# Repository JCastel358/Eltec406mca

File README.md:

# Eltec sensor test rigs

Bench rigs and software that qualify Eltec pyroelectric IR sensors. Two rigs
live in this repository, one top-level folder each:

- **`single_detector_rig/`** — an ESP32 chops an IR emitter and streams a
  24-bit ADS1256 ADC to a laptop; one Python desktop application runs the
  test procedure for the sensor model chosen in a dropdown, judges each part,
  and writes a CSV row per sensor.
- **`array_rig/`** — fifty detectors at once: a 50-position buffer PCB read
  by an ACCES USB-AIO16-64MA DAQ; the same selector-plus-model-directory
  structure, testing offset and noise per tray (sensitivity waits for the
  emitter board).

Windows 11 and Xubuntu are both supported.

The current **M25/HUB array** workflow is available from the normal Array Rig
launcher: selectable offset/noise tests, simultaneous recording at 80% settled
(90-second fallback), linked retests, persistent slot warnings, and saved
50-position reports. See [the current array instructions](array_rig/README.md).
Real M25/HUB acquisition uses Windows and the ACCES driver; simulation also
runs without hardware. No Arduino/ESP32 flash is needed for this offset/noise
check. Earlier contiguous-channel instructions are the explicit legacy profile.

| Sensor model | Procedure | Status (2026-09-02) | Results folder (`Documents\…`) |
| --- | --- | --- | --- |
| **405 M22** (1 Hz) | TP412 — offset, emitter-off noise, sensitivity/polarity | production; sensitivity factor 4.30 from lot 500 | `Eltec_405M22_Test_Results\405m22_esp32` |
| **406 MCA** (10 Hz) | offset, sensitivity/polarity, v6.1 stability policy | production; factor 1.582 from lot 520 | `Eltec_406MCA_Test_Results\v6_1_esp32` |
| **449 M18** (5 + 18 Hz) | TP443 frequency tracking | **calibration pending** (K_5 / K_18 not derived; needs firmware v3.2, not yet flashed) | `Eltec_449M18_Test_Results\449m18_esp32` |
| **40623 array** (50 positions, DAQ) | TP120 offset check + noise, fifty at a time | **calibration pending** (noise limits not derived, offset limits provisional; raw captures saved for the paired lot) | `Eltec_40623_Test_Results\40623_array_daq` |

---

## Set up another Windows computer

1. Install **64-bit Python with Tcl/Tk and pip**, and enable its PATH option.
   The software check for this update used Python **3.14.5**. Install Git if
   you want to clone/pull updates; GitHub's Download ZIP also works.
2. Clone the repository, or run `git pull --ff-only` in an existing clean
   checkout. In PowerShell, from the repository root:

   ```powershell
   git clone -c core.longpaths=true https://github.com/JCastel358/Eltec406mca.git
   cd Eltec406mca
   python -m pip install -r requirements.txt
   python -c "import struct, tkinter, numpy, serial, matplotlib; print('Python bits:', struct.calcsize('P') * 8)"
   ```

   The clone option enables Git's Windows long-path support for the archived
   hardware exports. Keep the checkout path short; for an existing checkout,
   run `git config core.longpaths true` before pulling if Git reports
   "Filename too long". The bitness check must print **64** for real DAQ operation. Install into
   the same Python used to launch the app. If multiple Pythons are installed,
   set `ELTEC_PYTHON` to that interpreter's full executable path before using
   a `.cmd` launcher (the launchers otherwise prefer `pythonw.exe` on PATH).
3. For the **M25/HUB array**, install the ACCES **USB-AIO16-64MA driver
   package**, including the 64-bit `AIOUSB.dll`. Drivers are installed per PC
   and are not included in Git. This workflow runs on Windows and does not
   require Arduino, an ESP32 flash, or the separate `50AmpBoard` checkout.
   For the **single-detector rig**, install the board's USB-serial driver if
   needed and select its actual COM port; it may differ on the new computer.
4. Check the array dashboard without hardware first:

   ```powershell
   python array_rig/eltec_array_tester.py --simulate
   ```

   Choose **Generated demo** and complete a batch. To run normally, use
   `array_rig/run_eltec_array_tester.cmd`; the single-detector launcher is
   `single_detector_rig/run_eltec_rig_tester.cmd`. Optional desktop shortcuts
   are created by each rig's `install_windows_launcher.ps1` on the new PC.
   Before real acquisition, follow the current [array power/setup procedure](array_rig/README.md).
5. **Transfer saved data separately if needed.** Git does not contain the
   `Documents/Eltec_*_Test_Results/` folders, including results, raw captures,
   and reference calibration files. Preserve their directory structure and
   originals; see the [data and backup guide](array_rig/docs/DATA_MAP.md).
   A new physical setup still needs its applicable reference checks; copying
   files does not establish calibration for changed hardware.

The MOD50 browser dashboard and its assets are included in the repository
and run locally. Node.js and Playwright are only for optional browser
regression tests, not for operating the app. Python packages and device
drivers must be installed before offline use. Source files, firmware snapshots,
hardware packages and documentation are included; local `tmp/` runs, caches
and generated measurement data are not new Git content.

## I'm a technician — run a batch

1. Laptop on AC power, ESP32 USB cable in, both batteries connected, no fans near the fixture.
2. Double-click the **Eltec Test Rig** desktop icon (or `single_detector_rig\run_eltec_rig_tester.cmd` / `.sh`). For a tray of fifty on the array rig use the **Eltec Array Rig** icon (`array_rig\run_eltec_array_tester.cmd` / `.sh`) — runbook §3b.
3. Pick the sensor model → **Start tester** → batch number, your name, filter setup → load a part → **Enter**.
4. Read the banner (PASS / PASS · NEAR LIMIT / FAIL) → load the next sensor →
   **Next (Enter)**. The number only advances when a part passes.

Everything else — verdicts, the Stop / Next buttons, where files go,
what to do when something fails — is in
**[array_rig/docs/TECHNICIAN_RUNBOOK.md](array_rig/docs/TECHNICIAN_RUNBOOK.md)**.

## I'm the engineer taking over

Start with **[array_rig/docs/ENGINEER_HANDOVER.md](array_rig/docs/ENGINEER_HANDOVER.md)** (what
you are inheriting, architecture, the copy-per-model rule, firmware lifecycle,
open work). Then **[array_rig/docs/CALIBRATION_RECORD.md](array_rig/docs/CALIBRATION_RECORD.md)**
before touching any limit.

## Repository map

```
README.md                    this file — the index
CHANGELOG.md                 dated history, newest first (one entry per behavioural change)
CLAUDE.md                    ground rules for AI-assisted sessions
run_all_tests.py|.cmd|.sh    runs every test suite of both rigs, prints a summary
array_rig/docs/
  TECHNICIAN_RUNBOOK.md      operator instructions
  ENGINEER_HANDOVER.md       engineering manual + open work
  CALIBRATION_RECORD.md      every limit/factor/gate state with provenance  ← source of truth for numbers
  DATA_MAP.md                where results & evidence live (outside the repo) + backup routine
  TP120(40623).pdf           test procedure of the 40623 (array rig); daq_usb_aio16_64ma/ = DAQ vendor docs
single_detector_rig/         THE single-detector application — selector + one directory per sensor model
  eltec_rig_tester.py        selector GUI (dropdown → launches the model app)
  sensor_versions.py         model registry + required firmware
  attempt_history.py         per-batch attempt log (shared)
  v1_single_sensor/          vendored signal-math engine (shared, frozen)
  m405m22/ m406mca/ m449m18/ one qualified tester each: GUI, backend, analysis, tests, launchers, README
  run_eltec_rig_tester.*     launchers; install_*_launcher.* = optional desktop icon
array_rig/                   THE array application — selector + one directory per detector model (same pattern)
  eltec_array_tester.py      selector GUI (model dropdown → launches the model app)
  sensor_versions.py         model registry + required hardware (DAQ)
  tray_history.py            per-lot tray event log (shared)
  m40623/                    the 40623 build: GUI, DAQ backend (ctypes AIOUSB.dll), numpy noise port, probe, bench readout + live viewer, tests, launchers
Arduino/Eltec/               firmware (single rig today; the array rig's emitter board will use it later)
  Eltec.ino                  live sketch (v3.4)        README.md = protocol, flashing, troubleshooting
  versions/                  frozen copy of every build + which firmware belongs on which rig
  flash_firmware.py          one-command compile/upload/verify (+ run_flash_firmware.cmd/.sh)
  esp32_rig_readout.py, live_waveform.py   bench tools
  ESP32_ADS1256_Wiring_v2_0.md             current wiring (…_legacy_v1_9.md = retired standalone 406 rigs)
engineer_tools/              engineering-only tools, one folder per topic (README.md inside lists them)
  noise_band/                replot_noise_capture.py (replay raw noise captures under any band), filter_response_analysis.py
  array_parity/              array_noise_parity.py (derive the array rig's pin-level noise limits from a paired lot)
  emitter/                   emitter_waveform_comparison.py (legacy chopper vs rig emitter waveform shape)
  reference_unit/            reference_candidate_qualifier.py (pick the detector to mount as the AIN1 reference unit)
analysis/
  405M22_Data/               lot-500 paired-fixture data behind the 4.30 factor
  reports/                   noise-filtering explainer, historical buffer/SNR write-ups
assets/eltec_logo.png        logo loaded by the apps
```

Retired applications (LabJack-era v1–v4, ESP32 v5/v6/v6.1, the standalone
405m22 build, the pre-v2.0 unified app) were removed from the tree on
2026-08-28 and are preserved at git tag **`archive/pre-cleanup-2026-08-28`**:
`git show archive/pre-cleanup-2026-08-28:<path>`.

## Firmware

The current single-detector sketch is `Arduino/Eltec/Eltec.ino` **v3.4**;
the 449 M18 mode requires v3.2 or newer. Check the connected board before
deciding whether to flash. The array DAQ loads its firmware from the ACCES
driver package and needs no ESP32 update. Check the single-detector firmware:

```
python Arduino/Eltec/flash_firmware.py --check
```

For a unified single-detector board that needs updating (legacy standalone
406 rigs stay on v1.9), compile, flash and verify with:

```
python Arduino/Eltec/flash_firmware.py          # --check to only ask what the board runs
```

Firmware guide: [Arduino/Eltec/README.md](Arduino/Eltec/README.md). Which
build belongs on which rig (legacy 406 rigs stay on v1.9):
[Arduino/Eltec/versions/README.md](Arduino/Eltec/versions/README.md).

## Tests

```
python run_all_tests.py
```

Seven `unittest` suites cover the live viewer, single-detector rigs and array
rig, without hardware. On Windows the 406 MCA suite has one known
environment-only installer case (it passes on Xubuntu); the runner reports
it separately. Any other failure makes the runner fail.

## Where the data is

Results, attempt logs, waveform snapshots, raw noise captures and calibration
files are written **outside this repository** under
`Documents\Eltec_<model>_Test_Results\`. They are the only copy of the evidence
behind the production constants — the backup routine is in
[array_rig/docs/DATA_MAP.md](array_rig/docs/DATA_MAP.md).

## Documentation index

| Document | Audience | Contents |
| --- | --- | --- |
| [array_rig/docs/TECHNICIAN_RUNBOOK.md](array_rig/docs/TECHNICIAN_RUNBOOK.md) | technician | start, run a batch, read verdicts, troubleshoot |
| [array_rig/docs/ENGINEER_HANDOVER.md](array_rig/docs/ENGINEER_HANDOVER.md) | engineer | architecture, policies, procedures, open work, conventions |
| [array_rig/docs/CALIBRATION_RECORD.md](array_rig/docs/CALIBRATION_RECORD.md) | engineer | constants + provenance + gate states per model |
| [array_rig/docs/DATA_MAP.md](array_rig/docs/DATA_MAP.md) | engineer | results layout, evidence, backup |
| [single_detector_rig/README.md](single_detector_rig/README.md) | engineer | the selector app, launchers, v2.0 skip/attempt features |
| [m405m22/README.md](single_detector_rig/m405m22/README.md) · [m406mca/README.md](single_detector_rig/m406mca/README.md) · [m449m18/README.md](single_detector_rig/m449m18/README.md) | engineer | per-model test mechanics |
| [array_rig/README.md](array_rig/README.md) · [m40623/README.md](array_rig/m40623/README.md) | engineer | the array rig: selector, DAQ chain, the 40623 flow, colours, files, PENDING status, the engineering tools (bench probe, readout, live viewer) |
| [array_rig/docs/TP120(40623).pdf](array_rig/docs/TP120(40623).pdf) · [array_rig/docs/daq_usb_aio16_64ma/](array_rig/docs/daq_usb_aio16_64ma/) | engineer | the 40623 test procedure; DAQ datasheet, DAQ-PACK guide, letter of volatility |
| [Arduino/Eltec/README.md](Arduino/Eltec/README.md) · [versions/README.md](Arduino/Eltec/versions/README.md) | engineer | firmware, protocol, flashing, version archive |
| [CHANGELOG.md](CHANGELOG.md) | both | what changed, when, why |

## Dependencies

Python 3 with `tkinter`, `numpy`, `pyserial`, `matplotlib` (optional, nicer
snapshots). The array rig additionally needs the ACCES **USB-AIO16-64MA
Install** driver package (provides `AIOUSB.dll`) and a **64-bit** Python; no
extra Python packages. Xubuntu: `sudo apt install python3 python3-tk python3-numpy
python3-serial python3-matplotlib`, user in `dialout`. Flashing needs the
Arduino IDE 2.x installed (its bundled `arduino-cli` is used).

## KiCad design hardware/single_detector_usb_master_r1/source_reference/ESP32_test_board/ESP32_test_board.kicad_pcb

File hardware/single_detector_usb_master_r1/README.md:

# Single detector rig — USB master power, revision 1

**Routed engineering prototype candidate. Not a fabrication release.**

This separate project replaces the supplied ESP32 carrier while preserving the original files in `source_reference/`. Its required behavior is that the upstream USB switch starts and stops the complete rig, including both HeyFuture LiFePO4 6.4 V, 6 Ah battery domains, with the ADC protected throughout startup and shutdown. The emitter maximum stated current is 200 mA. Component selection is independent of the IRLB8748s available for the earlier perfboard idea.

The deliverable is an editable, electrically connected KiCad design with routed PCB, project libraries, assembly BOM/CPL, assembly views, draft fabrication exports, and reproducible ERC/DRC/parity checks. All physical board components are to be populated except the ESP32 module, ADS1256 module, and two barrel jacks. Module sockets are populated components. Original wire solder lands are copper features, not fictitious purchased parts.

Use `PLAN.md` for milestone status, `DECISIONS.md` for choices and assumptions, and `research/` for source-backed engineering evidence. Reports must identify the design revision/hash they validate. Absence of an error report is not a pass.

The original board is 86 × 103 mm. Until mating-part and enclosure evidence is confirmed, trial layouts using those coordinates remain preliminary. No enclosure fit, prototype timing, actual module internals, production sourcing, or manufacturing release is implied by CAD checks.

The trial outline is 86 × 145 mm, growing only perpendicular to the ESP32's
long axis. The 213-symbol schematic passes native ERC and 272 exported
connectivity checks. All 15 schematic PDF pages have been visually reviewed.
The 206-footprint, four-layer board is fully routed: native KiCad 10.0.6 reports
zero DRC violations, zero unrouted connections and zero schematic mismatches
after filling its ten ground/thermal zones. Exact report hashes identify the
checked revision. These are CAD results; physical sequencing is not yet tested.

Start with `single_detector_usb_master/single_detector_usb_master.kicad_pro`.
Keep the adjacent `libraries/` directory with the project. `REPRODUCE.md`
describes validation; `BRINGUP.md` records the unperformed hardware checks.
Use the separate `firmware/Eltec_USB_Master/Eltec_USB_Master.ino` for the R1
carrier after confirming the ESP32 configuration. It compiled and passed 24
host-protocol checks; nothing was flashed.

The draft assembly contains 195 fitted components in 68 BOM groups. Seven exact
manufacturer part numbers (nine references) need JLC catalog/sourcing
confirmation, and C12's identified catalog entry was out of stock at the public
check. Prepared sourcing requests are in `research/global_sourcing_prepared.csv`;
none was submitted. All vendor placement rotations still need assembly-preview
confirmation. These files are not an immediately approved populated-board order.

Mechanical fit, actual battery endpoints, module internals, USB switch behavior,
thermal performance and measurement calibration remain unverified. In particular,
the stacked static ADC supply corner leaves only 4.64 mV below its 5.25 V
operating ceiling; actual module AVDD transients must be measured before using
the prototype for accepted detector measurements.

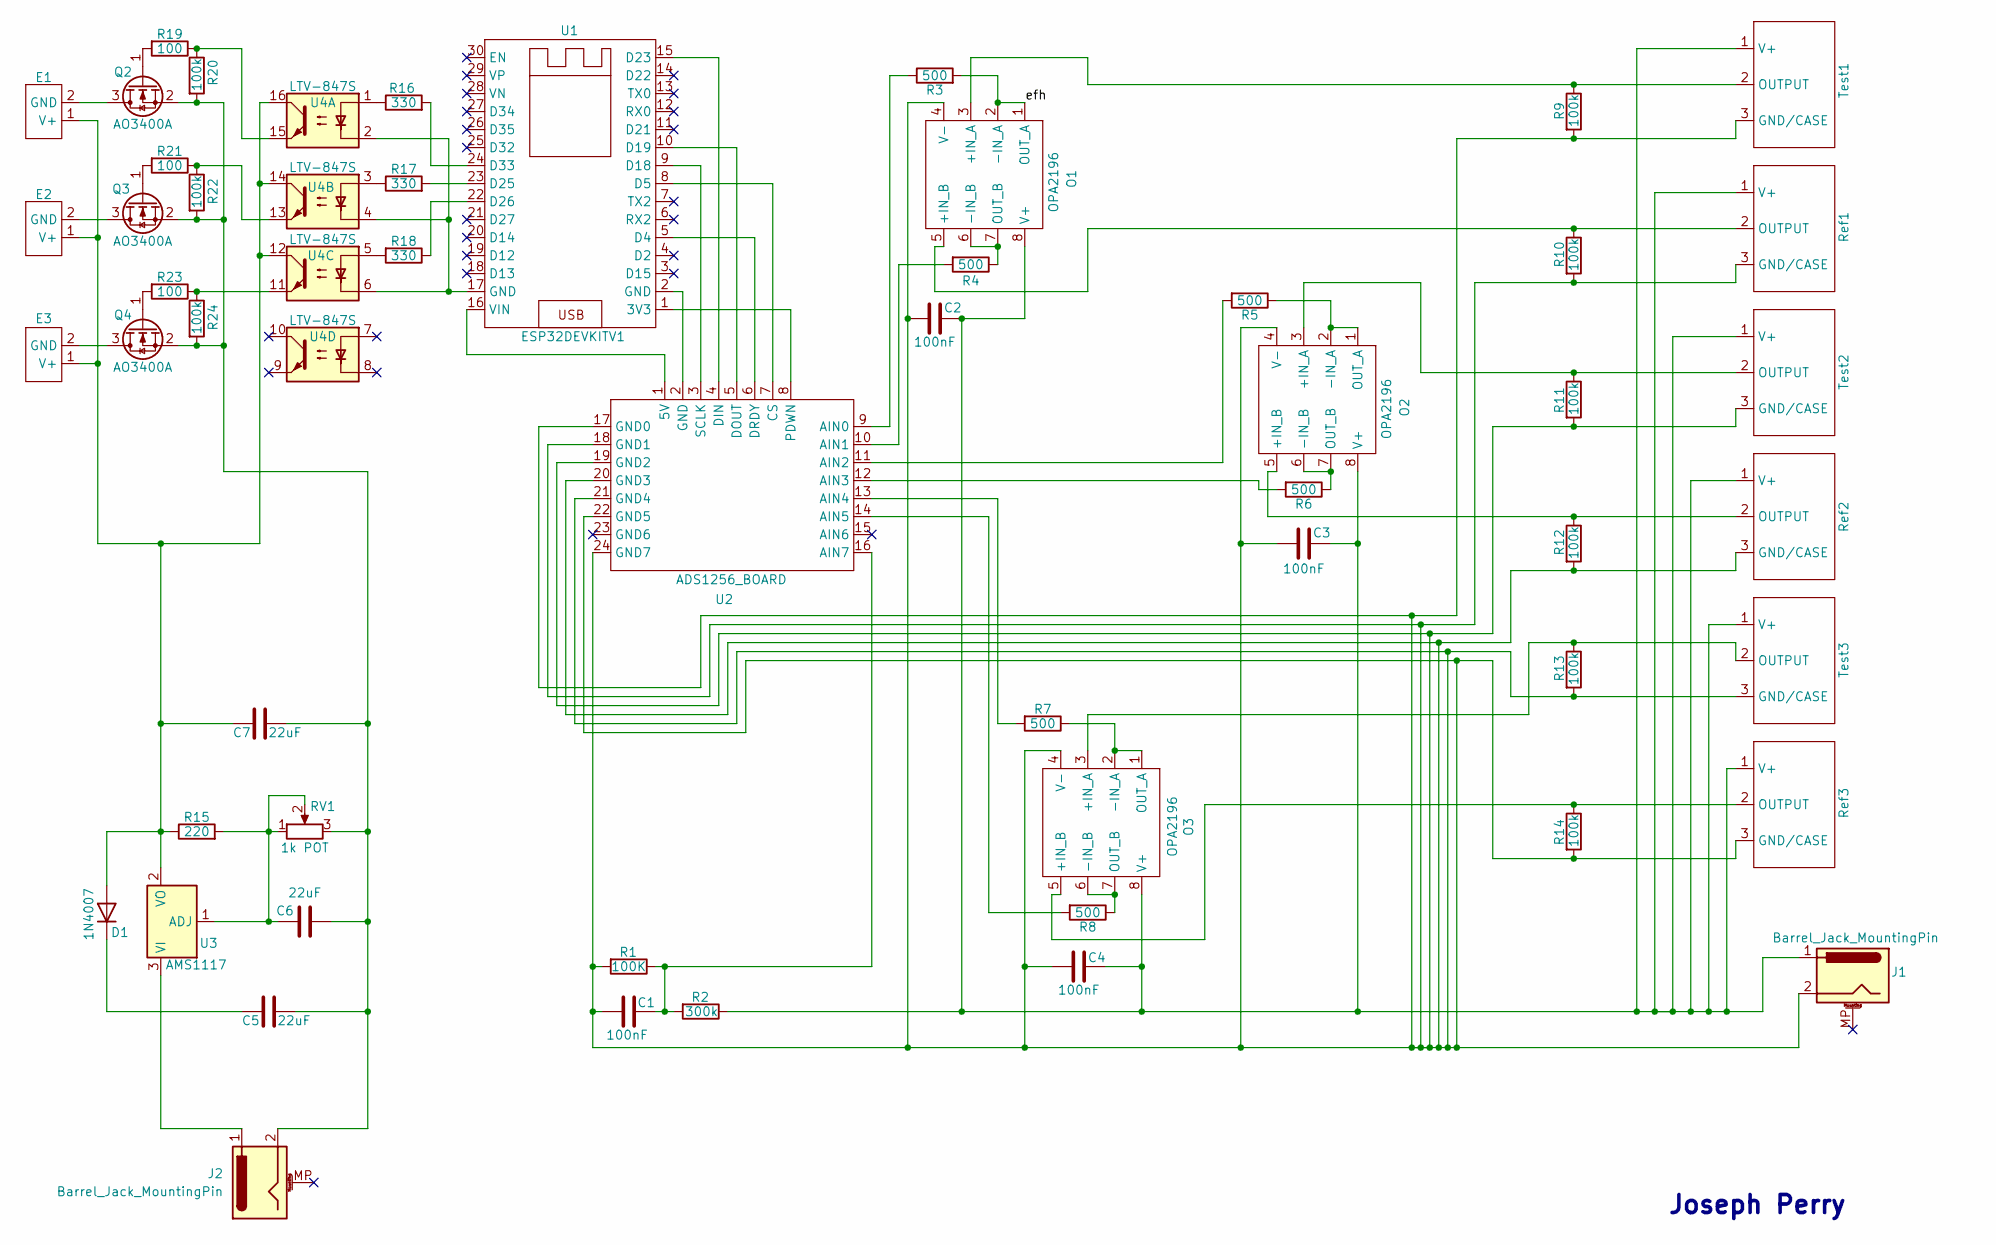
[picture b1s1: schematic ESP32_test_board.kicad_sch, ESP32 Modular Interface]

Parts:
C1, C2, C3, C4: 100nF; C_0805_2012Metric
C5, C6, C7: 22uF; C_1206_3216Metric
D1: 1N4007; D_SOD-123
E1, E2, E3: IR-56; Emitter
J1, J2: Barrel_Jack_MountingPin; BarrelJack_GCT_DCJ200-10-A_Horizontal
O1, O2, O3: OPA2196; SOIC-8_3.9x4.9mm_P1.27mm
Q2, Q3, Q4: AO3400A; SOT-23
R1: 100K; R_0805_2012Metric
R2: 300k; R_0805_2012Metric
R3, R4, R5, R6, R7, R8: 500; R_0805_2012Metric
R9, R10, R11, R12, R13, R14, R20, R22, R24: 100k; R_0805_2012Metric
R15: 220; R_0805_2012Metric
R16, R17, R18: 330; R_0805_2012Metric
R19, R21, R23: 100; R_0805_2012Metric
RV1: 1k POT; Potentiometer_Bourns_3296W_Vertical
Ref1, Ref2, Ref3: Sensor
Test1, Test2, Test3: Sensor
U1: ESP32DEVKITV1; ESP32_DEVKITV1
U2: ADS1256_BOARD
U3: AMS1117; SOT-223-3_TabPin2
U4: LTV-847S; SMDIP-16_W9.53mm

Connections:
unnamed: C7.2, D1.2 (A), E1.1 (V+), E2.1 (V+), E3.1 (V+), R15.1, U3.2 (VO), U4.12, U4.14, U4.16
unnamed: C5.2, D1.1 (K)
unnamed: E1.2 (GND), Q2.3 (D)
unnamed: E2.2 (GND), Q3.3 (D)
unnamed: E3.2 (GND), Q4.3 (D)
unnamed: O1.3 (+IN_A), R9.1, Test1.2 (OUTPUT)
unnamed: O1.5 (+IN_B), R10.1, Ref1.2 (OUTPUT)
unnamed: O1.1 (OUT_A), O1.2 (-IN_A), R3.2
unnamed: O1.6 (-IN_B), O1.7 (OUT_B), R4.1
unnamed: C2.1, C3.1, C4.1, J1.1, O1.8 (V+), O2.8 (V+), O3.8 (V+), R2.1, Ref1.1 (V+), Ref2.1 (V+), Ref3.1 (V+), Test1.1 (V+), Test2.1 (V+), Test3.1 (V+)
unnamed: C1.2, C2.2, C3.2, C4.2, J1.2, O1.4 (V-), O2.4 (V-), O3.4 (V-), R1.2, R9.2, R10.2, R11.2, R12.2, R13.2, R14.2, Ref1.3 (GND/CASE), Ref2.3 (GND/CASE), Ref3.3 (GND/CASE), Test1.3 (GND/CASE), Test2.3 (GND/CASE), Test3.3 (GND/CASE), U2.17 (GND0), U2.18 (GND1), U2.19 (GND2), U2.20 (GND3), U2.21 (GND4), U2.22 (GND5), U2.24 (GND7)
unnamed: O2.3 (+IN_A), R11.1, Test2.2 (OUTPUT)
unnamed: O2.5 (+IN_B), R12.1, Ref2.2 (OUTPUT)
unnamed: O2.1 (OUT_A), O2.2 (-IN_A), R5.1
unnamed: O2.6 (-IN_B), O2.7 (OUT_B), R6.1
unnamed: O3.3 (+IN_A), R13.1, Test3.2 (OUTPUT)
unnamed: O3.5 (+IN_B), R14.1, Ref3.2 (OUTPUT)
unnamed: O3.1 (OUT_A), O3.2 (-IN_A), R7.1
unnamed: O3.6 (-IN_B), O3.7 (OUT_B), R8.1
unnamed: Q2.1 (G), R19.2
unnamed: C5.1, C6.1, C7.1, J2.2, Q2.2 (S), Q3.2 (S), Q4.2 (S), R20.2, R22.2, R24.2, RV1.3
unnamed: Q3.1 (G), R21.2
unnamed: Q4.1 (G), R23.2
unnamed: R16.1, U4.1
unnamed: R17.1, U4.3
unnamed: R18.2, U4.5
unnamed: R19.1, R20.1, U4.15
unnamed: R21.1, R22.1, U4.13
unnamed: R23.1, R24.1, U4.11
unnamed: U1.1 (3V3), U2.8 (PDWN)
unnamed: U1.5 (D4), U2.6 (DRDY)
unnamed: U1.8 (D5), U2.7 (CS)
unnamed: U1.9 (D18), U2.3 (SCLK)
unnamed: U1.10 (D19), U2.5 (DOUT)
unnamed: U1.15 (D23), U2.4 (DIN)
unnamed: R17.2, U1.23 (D25)
unnamed: R18.1, U1.22 (D26)
unnamed: R16.2, U1.24 (D33)
unnamed: U1.17 (GND), U4.2, U4.4, U4.6
unnamed: U1.16 (VIN), U2.1 (5V)
unnamed: R3.1, U2.9 (AIN0)
unnamed: R4.2, U2.10 (AIN1)
unnamed: R5.2, U2.11 (AIN2)
unnamed: R6.2, U2.12 (AIN3)
unnamed: R7.2, U2.13 (AIN4)
unnamed: R8.2, U2.14 (AIN5)
unnamed: C1.1, R1.1, R2.2, U2.16 (AIN7)
unnamed: U1.2 (GND), U2.2 (GND)
unnamed: C6.2, R15.2, RV1.1, RV1.2, U3.1 (ADJ)
unnamed: J2.1, U3.3 (VI)

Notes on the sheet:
Joseph Perry

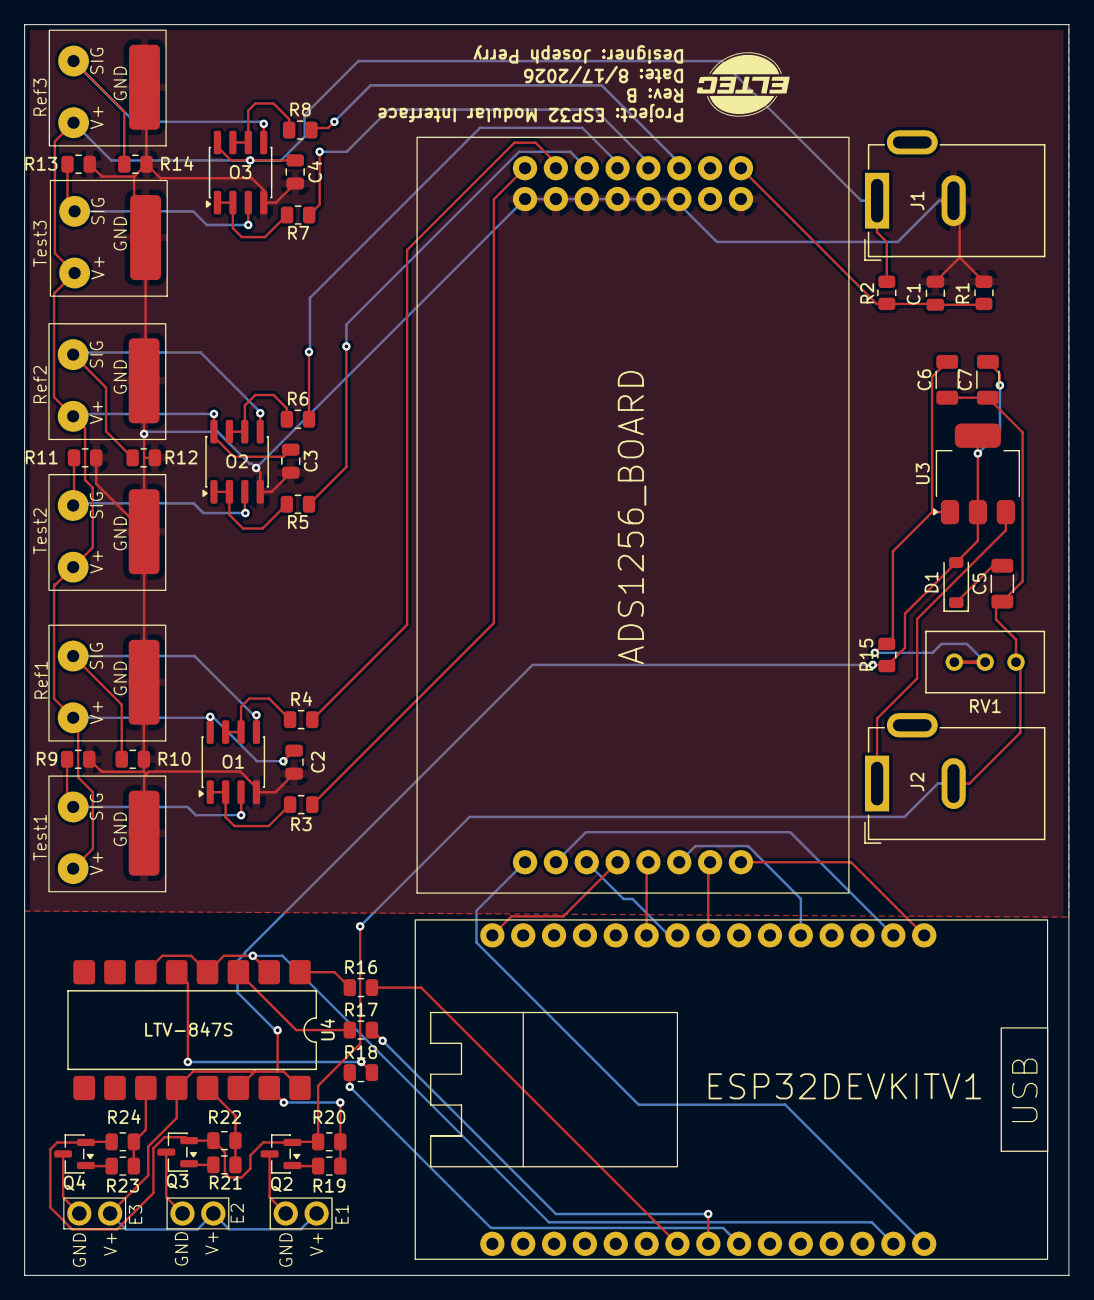
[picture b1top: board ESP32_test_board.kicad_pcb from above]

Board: 2 copper layers, 86.0 x 103.0 mm, 54 parts (0 on the bottom side), 50 nets.

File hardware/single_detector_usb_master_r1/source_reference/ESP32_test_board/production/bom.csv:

Designator,Footprint,Quantity,Value,LCSC Part #
"C1, C2, C3, C4",805,4,100nF,C49678
"C5, C6, C7",1206,3,22uF,C12891
D1,D_SOD-123,1,1N4007,C2892681
"O1, O2, O3",SOIC-8_3.9x4.9mm_P1.27mm,3,OPA2196,C2057972
"Q2, Q3, Q4",SOT-23,3,AO3400A,C20917
"R1, R10, R11, R12, R13, R14, R20, R22, R24, R9",805,10,100K,C149504
R15,805,1,220,C17557
"R16, R17, R18",805,3,330,C17630
"R19, R21, R23",805,3,100,C17408
R2,805,1,300k,C17616
"R3, R4, R5, R6, R7, R8",805,6,500,C2828857
U3,SOT-223-3_TabPin2,1,AMS1117,C6188
U4,SMDIP-16_W9.53mm,1,LTV-847S,C114599

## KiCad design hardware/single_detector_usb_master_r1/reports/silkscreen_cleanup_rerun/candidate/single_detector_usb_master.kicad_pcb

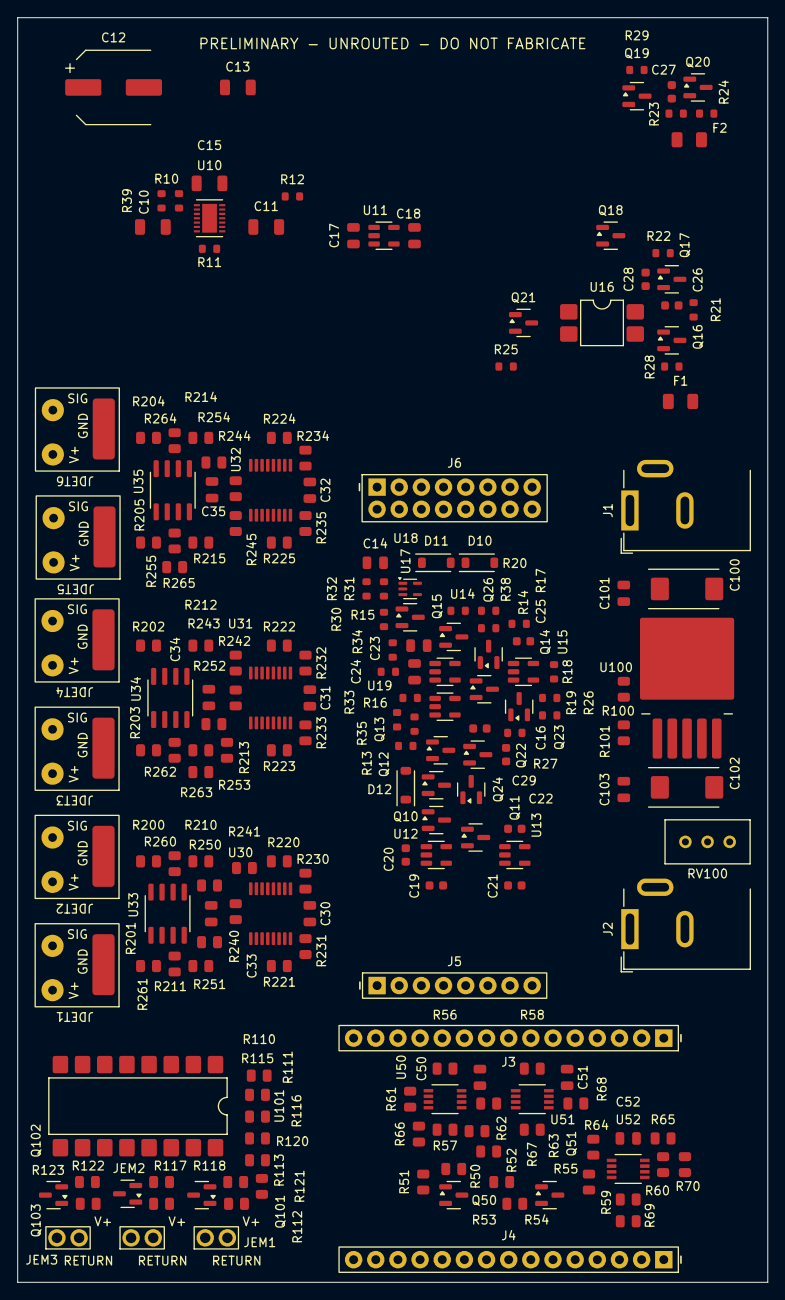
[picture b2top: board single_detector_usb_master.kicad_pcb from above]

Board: 4 copper layers, 86.0 x 145.0 mm, 201 parts (0 on the bottom side), 127 nets, no tracks yet.

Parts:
C10, C11, C13: 10uF 16V X7R; C_1206_3216Metric
C12: 820uF 6.3V polymer +/-20%; CP_Elec_8x11.9
C14, C23, C24: 100nF 5% C0G; C_0805_2012Metric
C15: 4.7uF 16V X7R; C_1206_3216Metric
C16, C19, C21, C25, C26, C27, C28, C29: 100nF 25V X7R; C_0603_1608Metric
C17, C18: 1uF 16V X7R; C_0805_2012Metric
C20, C22: 10nF 5% C0G; C_0603_1608Metric
C30, C31, C32, C33, C34, C35, C50, C51, C52: 100nF 16V X7R; C_0805_2012Metric
C100, C102: 22uF 25V 10% TPS; CP_EIA-7343-31_Kemet-D
C101, C103: 100nF 50V X7R 10%; C_0805_2012Metric
D10, D11: 1N4148W; D_SOD-123
D12: BZT52C6V8-7-F; D_SOD-123
F1: 1A Slo-Blo; Fuse_1206_3216Metric
F2: 1.5A Slo-Blo; Fuse_1206_3216Metric
J1, J2: GCT DCJ200-10-A / customer installed; BarrelJack_GCT_DCJ200_10_A
J3: 1x15 female socket - row A; Socket_Kinghelm_1x15_P2.54_H8.5
J4: 1x15 female socket - row B; Socket_Kinghelm_1x15_P2.54_H8.5
J5: 1x8 female ADC digital socket; Socket_Kinghelm_1x08_P2.54_H8.5
J6: 2x8 female ADC analog socket; Socket_FG_2x08_P2.54_H8.5
JDET1, JDET3, JDET5: TEST; Detector_Wire_Lands
JDET2, JDET4, JDET6: REFERENCE; Detector_Wire_Lands
JEM1: EMITTER 1; Emitter_Wire_Lands
JEM2: EMITTER 2; Emitter_Wire_Lands
JEM3: EMITTER 3; Emitter_Wire_Lands
Q10, Q11, Q23, Q24, Q26: AO3414; SOT-23
Q12, Q13, Q14, Q15, Q18, Q21: 2N7002LT1G; SOT-23
Q16, Q17, Q19, Q20: AO3401A; SOT-23
Q22, Q101, Q102, Q103: AO3400A; SOT-23
Q50, Q51: MMBT3904LT1G; SOT-23
R10: 51.1k 0.1% 10ppm/K; R_0603_1608Metric
R11: 300 0.1%; R_0603_1608Metric
R12, R20: 4.7k 1%; R_0603_1608Metric
R13, R18, R21, R23, R33, R38: 10k 1%; R_0603_1608Metric
R14, R15, R27, R28, R29, R34, R35: 100k 1%; R_0603_1608Metric
R16, R17, R22, R24: 1k 1%; R_0603_1608Metric
R19: 0; R_0603_1608Metric
R25: 390 1%; R_0603_1608Metric
R26: 100 1%; R_0603_1608Metric
R30: 1.5k 1%; R_0603_1608Metric
R31: 221 0.1% 25ppm/K; R_0603_1608Metric
R32: 1.00k 0.1% 25ppm/K; R_0603_1608Metric
R39: 698 0.1% 10ppm/K; R_0603_1608Metric
R50, R52, R53, R55, R61, R62, R63, R64, R65, R66, R67, R68, R69, R70: 10k; R_0805_2012Metric
R51, R54: 100k; R_0805_2012Metric
R56, R57, R58, R59, R60: 33; R_0805_2012Metric
R100: 210R 1% 0.125W; R_0805_2012Metric
R101: 7R5 1% 0.125W; R_0805_2012Metric
R110, R115, R120: 240R 1% 0.125W; R_0805_2012Metric
R111, R116, R121: 100k 1% 0.125W; R_0805_2012Metric
R112, R117, R122: 100R 1% 0.125W; R_0805_2012Metric
R113, R118, R123: 10k 1% 0.125W; R_0805_2012Metric
R200, R201, R202, R203, R204, R205: 100k 1%; R_0805_2012Metric
R210, R211, R212, R213, R214, R215: 10k 1%; R_0805_2012Metric
R220, R221, R222, R223, R224, R225, R250, R251, R252, R253, R254, R255: 499R 0.1%; R_0805_2012Metric
R230, R231, R232, R233, R234, R235: 220R 1%; R_0805_2012Metric
R240, R241, R242, R243, R244, R245, R260, R261, R262, R263, R264, R265: 33k 0.1%; R_0805_2012Metric
RV100: 1k 25-turn 0.5W; Potentiometer_Bourns_3296W_Vertical
U10: LT3041ADE#TRPBF; DFN-14-1EP_3x4mm_P0.5mm_EP1.7x3.3mm
U11: AP2112K-3.3TRG1; SOT-23-5
U12: TPS3840PL42DBVR; SOT-23-5
U13: TPS3840PL30DBVR; SOT-23-5
U14: TPS3840PL34DBVR; SOT-23-5
U15: SN74LVC1G14DBVR; SOT-23-5
U16: LTV-817S-B; SMDIP-4_W7.62mm
U17: LM4050AIM3-4.1/NOPB; SOT-23
U18: TLV3601DCKR; SOT-353_SC-70-5
U19: SN74LVC1G132DBVR; SOT-23-5
U30, U31, U32: ADG4613BRUZ; TSSOP-16_4.4x5mm_P0.65mm
U33, U34, U35: OPA2325IDR; SOIC-8_3.9x4.9mm_P1.27mm
U50, U51, U52: SN74LVC2G125DCTR; TI_DCT0008A_SSOP8
U100: LT1963AEQ#PBF; TO-263-5_TabPin3
U101: LTV-847S; SMDIP-16_W9.53mm

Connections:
ADC_5V_HELD: C11.1, C12.1, C13.1, C16.1, C17.1, C23.1, C30.1, C31.1, C32.1, C33.1, C34.1, C35.1, D11.2, J5.1, R12.1, R17.1, R30.1, R31.1, R38.1, U10.12, U10.13, U10.14, U11.1, U11.3, U18.5, U30.13, U31.13, U32.13, U33.8, U34.8, U35.8
ADC_AIN0: J6.1, R240.1, U30.2, U30.15
ADC_AIN1: J6.3, R241.1, U30.7, U30.10
ADC_AIN2: J6.5, R242.1, U31.2, U31.15
ADC_AIN3: J6.7, R243.1, U31.7, U31.10
ADC_AIN4: J6.9, R244.1, U32.2, U32.15
ADC_AIN5: J6.11, R245.1, U32.7, U32.10
ADC_COMPARATOR_GOOD: R16.1, U18.1
ADC_CS_DRV: R58.1, U51.6
ADC_CS_N: J5.7, R58.2, R68.1
ADC_DRDY_N: J5.6, R65.1, U52.5
ADC_IF_OE_N: Q50.3, R52.2, U50.1, U50.7, U51.1
ADC_IO_3V3: C18.1, C25.1, C50.1, C51.1, R20.1, R25.1, R52.1, R68.2, U11.5, U15.5, U50.8, U51.7, U51.8
ADC_LDO_ILIM: R11.1, U10.7
ADC_LDO_SET: C15.1, R10.1, U10.9
ADC_LDO_SET_RETURN: R10.2, R39.1
ADC_MISO: J5.5, R64.1, U52.2
ADC_MOSI: J5.4, R57.2, R67.1
ADC_MOSI_DRV: R57.1, U50.3
ADC_OE_BASE: Q50.1, R50.2, R51.1
ADC_PDWN_N: J5.8, Q15.3, R20.2
ADC_RAIL_SENSE: R31.2, R32.1, U18.3
ADC_READY_RAW: Q14.1, Q18.1, Q21.1, Q23.3, Q24.3, R16.2, R35.1, U19.1
ADC_REG_EN: Q12.3, R14.2, U10.5
ADC_SCLK: J5.3, R56.2, R66.1
ADC_SCLK_DRV: R56.1, U50.6
ADC_SUP_CT: C24.1, U14.5
ADC_SUP_MR_N: Q13.3, R15.2, U14.4
AMP_FB0: R250.2, R260.1, U33.2
AMP_FB1: R251.2, R261.1, U33.6
AMP_FB2: R252.2, R262.1, U34.2
AMP_FB3: R253.2, R263.1, U34.6
AMP_FB4: R254.2, R264.1, U35.2
AMP_FB5: R255.2, R265.1, U35.6
AMP_IN0: R210.2, U33.3
AMP_IN1: R211.2, U33.5
AMP_IN2: R212.2, U34.3
AMP_IN3: R213.2, U34.5
AMP_IN4: R214.2, U35.3
AMP_IN5: R215.2, U35.5
AMP_OUT0: R220.1, R250.1, U33.1
AMP_OUT1: R221.1, R251.1, U33.7
AMP_OUT2: R222.1, R252.1, U34.1
AMP_OUT3: R223.1, R253.1, U34.7
AMP_OUT4: R224.1, R254.1, U35.1
AMP_OUT5: R225.1, R255.1, U35.7
AMP_SERIES0: R220.2, U30.14
AMP_SERIES1: R221.2, U30.11
AMP_SERIES2: R222.2, U31.14
AMP_SERIES3: R223.2, U31.11
AMP_SERIES4: R224.2, U32.14
AMP_SERIES5: R225.2, U32.11
CLAMP_GND0: R230.1, U30.3
CLAMP_GND1: R231.1, U30.6
CLAMP_GND2: R232.1, U31.3
CLAMP_GND3: R233.1, U31.6
CLAMP_GND4: R234.1, U32.3
CLAMP_GND5: R235.1, U32.6
DET_BAT_FUSED: F1.2, Q16.3
DET_BAT_PROTECTED: C10.1, C26.2, D10.2, Q16.2, Q17.2, R14.1, R21.2, U10.1, U10.2, U10.3, U10.8
DET_BAT_RAW: F1.1, J1.1
DET_MASTER_GATE: C26.1, Q17.1, R21.1, R22.1
DET_MASTER_SINK: Q18.3, R22.2
DET_RPOL_GATE: Q16.1, R28.1
EMIT1_LOW: JEM1.2, Q101.3
EMIT2_LOW: JEM2.2, Q102.3
EMIT3_LOW: JEM3.2, Q103.3
EM_ADJ: R100.1, R101.2, U100.5
EM_BAT_FUSED: F2.2, Q19.3
EM_BAT_PROTECTED: C27.2, Q19.2, Q20.2, R23.2
EM_BAT_RAW: F2.1, J2.1
EM_BAT_SW: C100.1, C101.1, Q20.3, U100.1, U100.2, U101.12, U101.14, U101.16
EM_GATE1: Q101.1, R112.2, R113.1
EM_GATE1_DRIVE: R112.1, U101.15
EM_GATE2: Q102.1, R117.2, R118.1
EM_GATE2_DRIVE: R117.1, U101.13
EM_GATE3: Q103.1, R122.2, R123.1
EM_GATE3_DRIVE: R122.1, U101.11
EM_GND: C100.2, C101.2, C102.2, C103.2, J2.2, Q101.2, Q102.2, Q103.2, R29.2, R100.2, R113.2, R118.2, R123.2, U16.3, U100.3
EM_LED1_A: R110.2, U101.1
EM_LED2_A: R115.2, U101.3
EM_LED3_A: R120.2, U101.5
EM_LED_ENABLE_GATE: Q22.1, R26.2, R27.1
EM_LED_RETURN: Q22.3, U101.2, U101.4, U101.6
EM_MASTER_GATE: C27.1, Q20.1, R23.1, R24.1
EM_MASTER_LED_A: R25.2, U16.1
EM_MASTER_LED_K: Q21.3, U16.2
EM_OPTO_C: R24.2, U16.4
EM_REG: C102.1, C103.1, JEM1.1, JEM2.1, JEM3.1, RV100.1, RV100.2, U100.4
EM_RPOL_GATE: Q19.1, R29.1
EM_TRIM_TOP: R101.1, RV100.3
ENABLE_AND_MID: Q10.2, Q11.3
ESP_3V3: C21.1, C29.1, C52.1, J3.1, R55.1, R63.2, U13.2, U13.4, U19.5, U52.8
ESP_CS_N: J3.8, R63.1, U51.2
ESP_DRDY: J3.5, R60.2, R70.1
ESP_DRDY_DRV: R60.1, U52.3
ESP_EMIT1: J4.9, R110.1, R111.1
ESP_EMIT2: J4.8, R115.1, R116.1
ESP_EMIT3: J4.7, R120.1, R121.1
ESP_IF_OE_N: Q51.3, R55.2, U52.1, U52.7
ESP_MISO: J3.10, R59.2, R69.1
ESP_MISO_DRV: R59.1, U52.6
ESP_MOSI: J3.15, R62.1, U50.5
ESP_OE_BASE: Q51.1, R53.2, R54.1
ESP_POWER_NOT_READY: J4.11, R33.1, U19.4
ESP_SCLK: J3.9, R61.1, U50.2
ESP_SUP_CT: C22.1, U13.5
ESP_VALID_RAW: Q11.1, U13.1
GND: C10.2, C11.2, C12.2, C13.2, C14.2, C15.2, C16.2, C17.2, C18.2, C19.2, C20.2, C21.2, C22.2, C24.2, C25.2, C28.2, C29.2, C30.2, C31.2, C32.2, C33.2, C34.2, C35.2, C50.2, C51.2, C52.2, D12.2, J1.2, J3.2, J4.2, J5.2, J6.2, J6.4, J6.6, J6.8, J6.10, J6.12, J6.13, J6.14, J6.15, J6.16, JDET1.3, JDET2.3, JDET3.3, JDET4.3, JDET5.3, JDET6.3, Q11.2, Q12.2, Q13.2, Q14.2, Q15.2, Q18.2, Q21.2, Q22.2, Q23.2, Q24.2, Q26.2, Q50.2, Q51.2, R11.2, R12.2, R18.2, R27.2, R28.2, R32.2, R33.2, R34.2, R35.2, R39.2, R51.2, R54.2, R61.2, R62.2, R64.2, R65.2, R66.2, R67.2, R69.2, R70.2, R111.2, R116.2, R121.2, R200.2, R201.2, R202.2, R203.2, R204.2, R205.2, R230.2, R231.2, R232.2, R233.2, R234.2, R235.2, R240.2, R241.2, R242.2, R243.2, R244.2, R245.2, R260.2, R261.2, R262.2, R263.2, R264.2, R265.2, U10.10, U10.11, U10.15, U11.2, U12.3, U13.3, U14.3, U15.3, U17.2, U17.3, U18.2, U19.3, U30.4, U30.5, U31.4, U31.5, U32.4, U32.5, U33.4, U34.4, U35.4, U50.4, U51.4, U51.5, U52.4
ISOLATE_H: Q14.3, Q15.1, R17.2, U15.2, U30.1, U30.8, U30.9, U30.16, U31.1, U31.8, U31.9, U31.16, U32.1, U32.8, U32.9, U32.16
MASTER_PERMIT: R18.1, R19.1, R26.1, U15.4
OFF_BIAS_RAIL: D10.1, D11.1, R13.1
POWER_OFF_NODE: D12.1, Q10.3, Q12.1, Q13.1, Q24.1, R13.2
PWR_REF_4V096: C14.1, R15.1, R30.2, U14.2, U17.1, U18.4
REF_NOT_READY: C23.2, Q23.1, Q26.3, R38.2
REF_READY_RAW: Q26.1, R34.1, U14.1, U19.2
SENSOR0: JDET1.2, R200.1, R210.1
SENSOR1: JDET2.2, R201.1, R211.1
SENSOR2: JDET3.2, R202.1, R212.1
SENSOR3: JDET4.2, R203.1, R213.1
SENSOR4: JDET5.2, R204.1, R214.1
SENSOR5: JDET6.2, R205.1, R215.1
SENSOR_BAT_SW: C28.1, JDET1.1, JDET2.1, JDET3.1, JDET4.1, JDET5.1, JDET6.1, Q17.3
SPI_PERMIT: R19.2, R50.1, R53.1
USB_PRESENT_5V: C19.1, J4.1, U12.2, U12.4
USB_SUP_CT: C20.1, U12.5
USB_VALID_RAW: Q10.1, U12.1

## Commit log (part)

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2026-05-21 Add 406MCA signal monitor
2026-05-28 Add 406MCA scope verification tester
2026-06-08 Organize 406MCA tester files
2026-06-09 Add engineer data analysis reports
